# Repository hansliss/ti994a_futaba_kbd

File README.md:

# ti994a_futaba_kbd
A Futaba MD PCB for TI-99/4a

Included is also a simple Arduino sketch for testing the keyboard. Connect the rows (pin 8,13,14,15,9,12 on the connector) to port C, the columns (pin 5, 4, 1, 2, 11, 3, 10, 7 on the connector) to port A, and pin 6 on the connector (ALPHA LOCK) to A0. You may have to experiment with the pin numbering; I can't verify the order.

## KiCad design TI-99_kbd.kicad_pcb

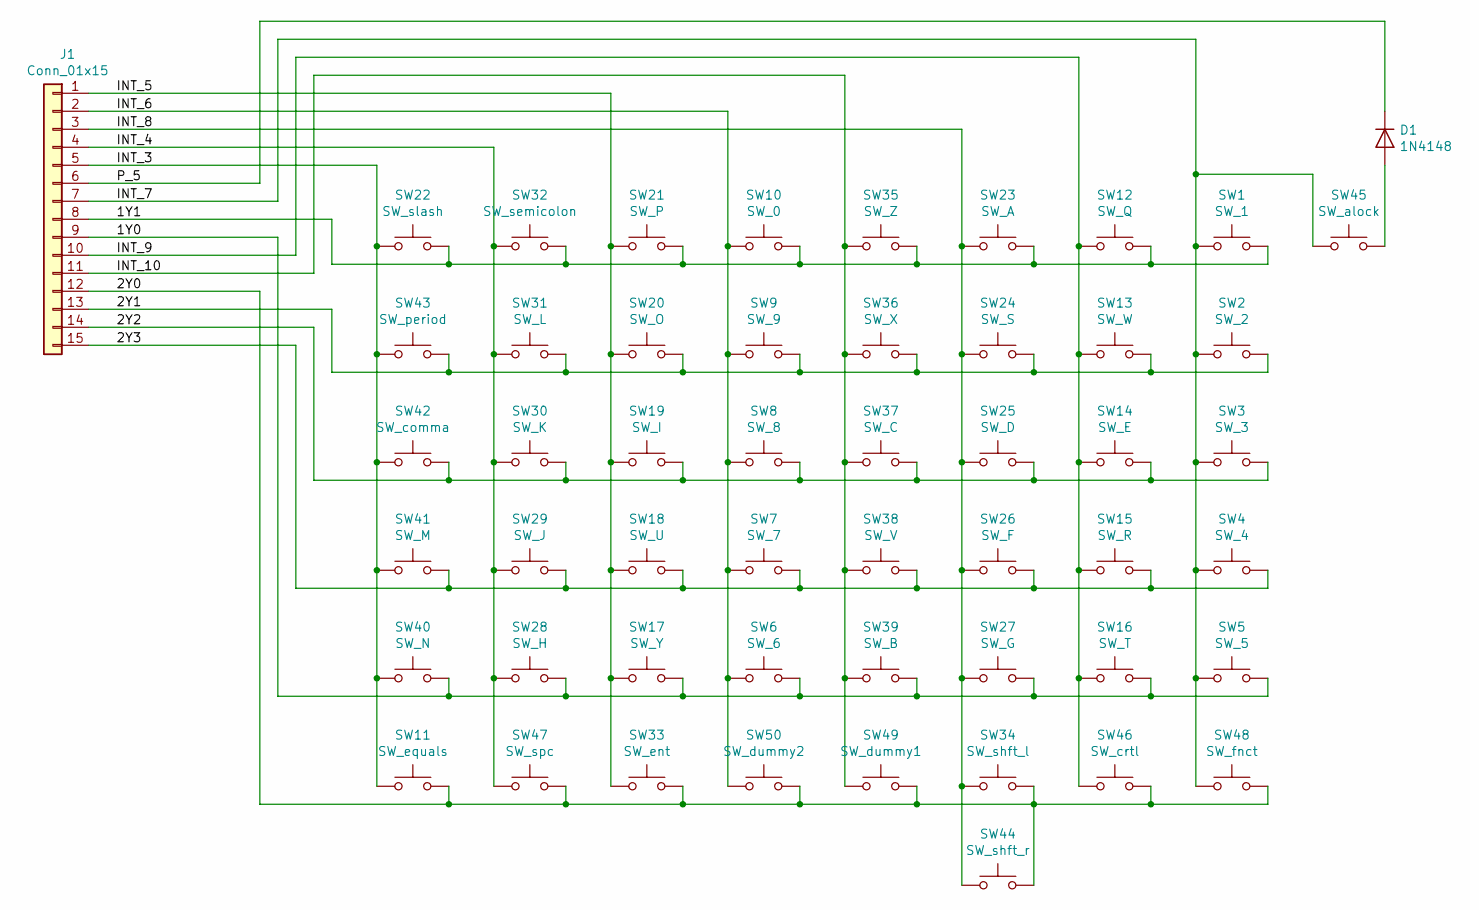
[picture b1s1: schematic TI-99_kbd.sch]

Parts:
D1: 1N4148; D_DO-35_SOD27_P7.62mm_Horizontal
J1: Conn_01x15; Pin_Header_Straight_1x15_Pitch2.54mm
SW1: SW_1; Futaba_MD_keyswitch
SW2: SW_2; Futaba_MD_keyswitch
SW3: SW_3; Futaba_MD_keyswitch
SW4: SW_4; Futaba_MD_keyswitch
SW5: SW_5; Futaba_MD_keyswitch
SW6: SW_6; Futaba_MD_keyswitch
SW7: SW_7; Futaba_MD_keyswitch
SW8: SW_8; Futaba_MD_keyswitch
SW9: SW_9; Futaba_MD_keyswitch
SW10: SW_0; Futaba_MD_keyswitch
SW11: SW_equals; Futaba_MD_keyswitch
SW12: SW_Q; Futaba_MD_keyswitch
SW13: SW_W; Futaba_MD_keyswitch
SW14: SW_E; Futaba_MD_keyswitch
SW15: SW_R; Futaba_MD_keyswitch
SW16: SW_T; Futaba_MD_keyswitch
SW17: SW_Y; Futaba_MD_keyswitch
SW18: SW_U; Futaba_MD_keyswitch
SW19: SW_I; Futaba_MD_keyswitch
SW20: SW_O; Futaba_MD_keyswitch
SW21: SW_P; Futaba_MD_keyswitch
SW22: SW_slash; Futaba_MD_keyswitch
SW23: SW_A; Futaba_MD_keyswitch
SW24: SW_S; Futaba_MD_keyswitch
SW25: SW_D; Futaba_MD_keyswitch
SW26: SW_F; Futaba_MD_keyswitch
SW27: SW_G; Futaba_MD_keyswitch
SW28: SW_H; Futaba_MD_keyswitch
SW29: SW_J; Futaba_MD_keyswitch
SW30: SW_K; Futaba_MD_keyswitch
SW31: SW_L; Futaba_MD_keyswitch
SW32: SW_semicolon; Futaba_MD_keyswitch
SW33: SW_ent; Futaba_MD_keyswitch
SW34: SW_shft_l; Futaba_MD_keyswitch
SW35: SW_Z; Futaba_MD_keyswitch
SW36: SW_X; Futaba_MD_keyswitch
SW37: SW_C; Futaba_MD_keyswitch
SW38: SW_V; Futaba_MD_keyswitch
SW39: SW_B; Futaba_MD_keyswitch
SW40: SW_N; Futaba_MD_keyswitch
SW41: SW_M; Futaba_MD_keyswitch
SW42: SW_comma; Futaba_MD_keyswitch
SW43: SW_period; Futaba_MD_keyswitch
SW44: SW_shft_r; Futaba_MD_keyswitch
SW45: SW_alock; Futaba_MD_keyswitch
SW46: SW_crtl; Futaba_MD_keyswitch
SW47: SW_spc; Futaba_MD_keyswitch
SW48: SW_fnct; Futaba_MD_keyswitch
SW49: SW_dummy1; SW_PUSH_6mm_h4.3mm
SW50: SW_dummy2; SW_PUSH_6mm_h4.3mm

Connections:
/1Y0: J1.9, SW5.2, SW6.2, SW16.2, SW17.2, SW27.2, SW28.2, SW39.2, SW40.2
/1Y1: J1.8, SW1.2, SW10.2, SW12.2, SW21.2, SW22.2, SW23.2, SW32.2, SW35.2
/2Y0: J1.12, SW11.2, SW33.2, SW34.2, SW44.2, SW46.2, SW47.2, SW48.2, SW49.2, SW50.2
/2Y1: J1.13, SW2.2, SW9.2, SW13.2, SW20.2, SW24.2, SW31.2, SW36.2, SW43.2
/2Y2: J1.14, SW3.2, SW8.2, SW14.2, SW19.2, SW25.2, SW30.2, SW37.2, SW42.2
/2Y3: J1.15, SW4.2, SW7.2, SW15.2, SW18.2, SW26.2, SW29.2, SW38.2, SW41.2
/INT_3: J1.5, SW11.1, SW22.1, SW40.1, SW41.1, SW42.1, SW43.1
/INT_4: J1.4, SW28.1, SW29.1, SW30.1, SW31.1, SW32.1, SW47.1
/INT_5: J1.1, SW17.1, SW18.1, SW19.1, SW20.1, SW21.1, SW33.1
/INT_6: J1.2, SW6.1, SW7.1, SW8.1, SW9.1, SW10.1, SW50.1
/INT_7: J1.7, SW1.1, SW2.1, SW3.1, SW4.1, SW5.1, SW45.1, SW48.1
/INT_8: J1.3, SW23.1, SW24.1, SW25.1, SW26.1, SW27.1, SW34.1, SW44.1
/INT_9: J1.10, SW12.1, SW13.1, SW14.1, SW15.1, SW16.1, SW46.1
/INT_10: J1.11, SW35.1, SW36.1, SW37.1, SW38.1, SW39.1, SW49.1
/P_5: D1.1 (K), J1.6
unnamed: D1.2 (A), SW45.2

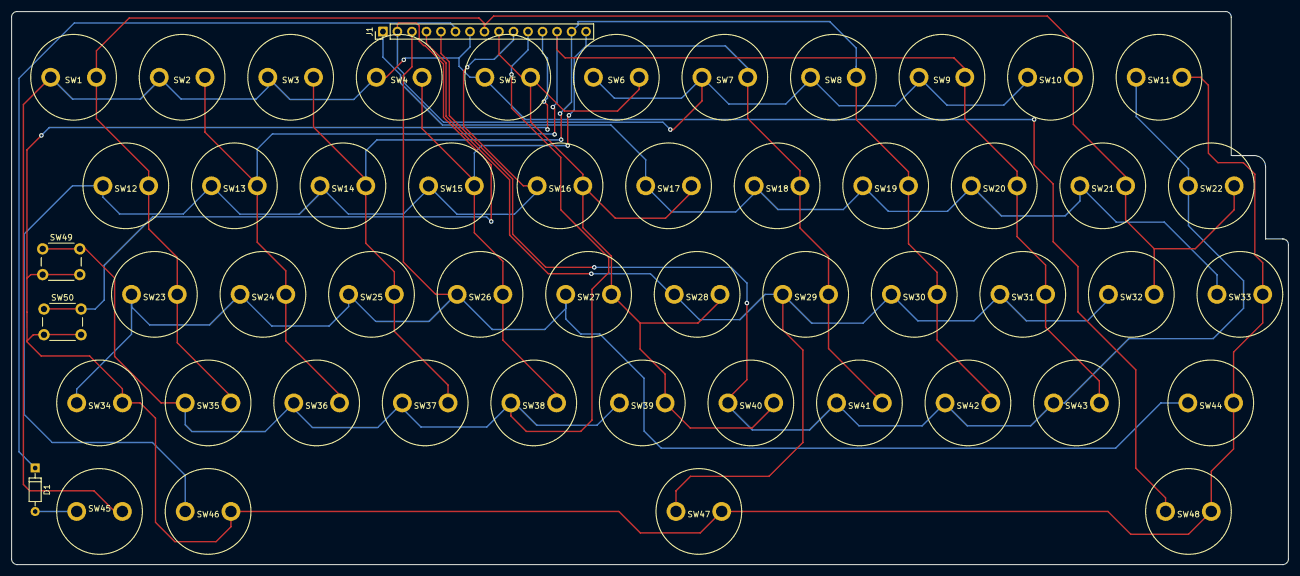
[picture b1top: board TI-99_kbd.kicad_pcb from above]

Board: 2 copper layers, 223.5 x 96.8 mm, 52 parts (0 on the bottom side), 16 nets.

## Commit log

2020-04-03 Initial import
2020-04-03 Removed Gerber archive; added Gerber files
2021-01-20 Added primitive Arduino code for testing.
2021-01-20 Updated readme with Arduino sketch info
